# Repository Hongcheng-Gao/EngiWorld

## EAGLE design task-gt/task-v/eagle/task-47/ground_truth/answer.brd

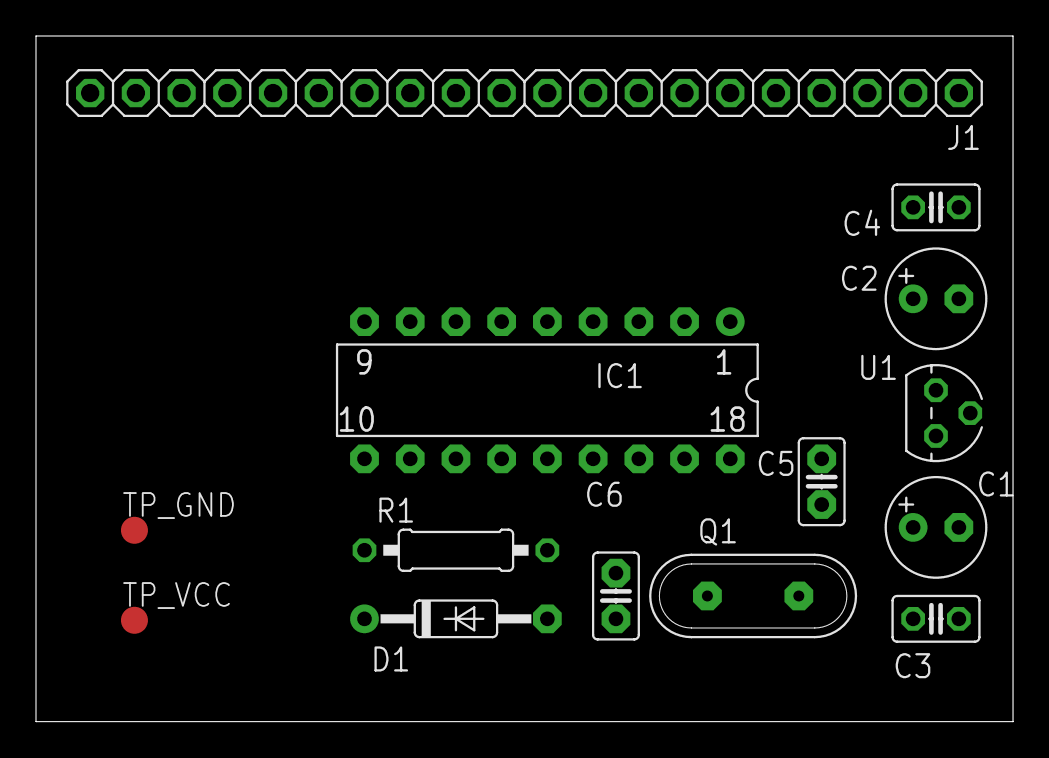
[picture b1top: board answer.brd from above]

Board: 2 copper layers, 54.3 x 38.1 mm, 14 parts (0 on the bottom side), 20 nets, no tracks yet.

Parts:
C1, C2: 10u; E2,5-6
C3, C4: 10n; C025-025X050
C5, C6: 27p; C2,5-2
D1: 1N4148; DO35-10
IC1: 16F84; DIL18
J1: 1X20
Q1: QS
R1: 2.2k; 0207/10
TP_GND: TP15R
TP_VCC: TP15R
U1: 78L05; TO92

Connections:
+12V: C1.+, C3.2, J1.2, U1.3
A0: IC1.17, J1.4
A1: IC1.18, J1.5
A2: IC1.1, J1.6
A3: IC1.2, J1.7
A4: IC1.3, J1.8
B0: IC1.6, J1.9
B1: IC1.7, J1.10
B2: IC1.8, J1.11
B3: IC1.9, J1.12
B4: IC1.10, J1.13
B5: IC1.11, J1.14
B6: IC1.12, J1.15, J1.18
B7: IC1.13, J1.16, J1.17
GND: C1.-, C2.-, C3.1, C4.1, C5.1, C6.1, IC1.5, J1.1, J1.20, TP_GND.TP, U1.2
unnamed: D1.K, IC1.4, J1.19
unnamed: D1.A, R1.1
unnamed: C5.2, IC1.16, Q1.2
unnamed: C6.2, IC1.15, Q1.1
VCC: C2.+, C4.2, IC1.14, J1.3, R1.2, TP_VCC.TP, U1.1

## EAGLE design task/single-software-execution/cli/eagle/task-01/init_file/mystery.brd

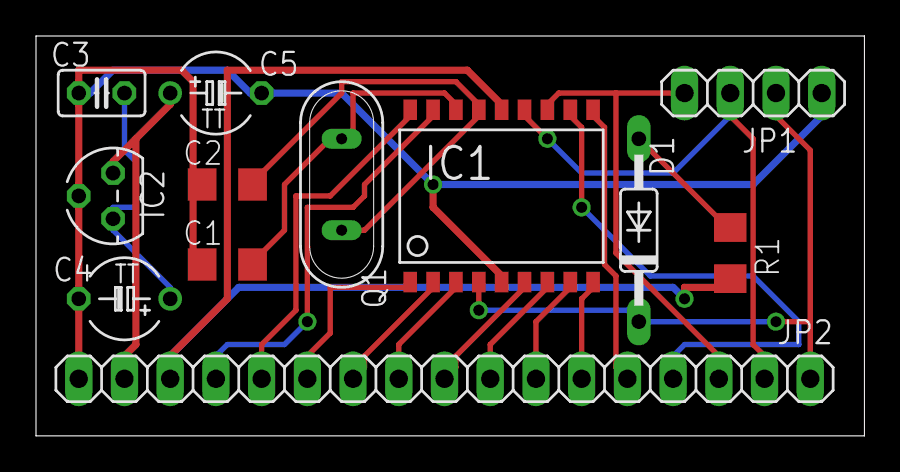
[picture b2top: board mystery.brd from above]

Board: 2 copper layers, 46.0 x 22.2 mm, 12 parts (0 on the bottom side), 21 nets.

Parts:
C1, C2: 30p; C1206
C3: 10n; C025-025X050
C4: 47u/25V; TAP5-45
C5: 47u; TAP5-45
D1: 1N4148; DO35-10
IC1: PIC16F84ASO; SO-18W
IC2: 78L05Z; TO92
JP1: PROG; 1X04
JP2: APPL; 1X17
Q1: QS
R1: 2,2k; R1206

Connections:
+5V: IC1.14, JP2.15, R1.1
GND: C1.1, C2.1, C3.2, C4.-, C5.-, IC1.5, IC2.2, JP1.4, JP2.17
MCLR/PGM: D1.C, IC1.4, JP1.3, JP2.1
unnamed: C3.1, C4.+, IC2.1
unnamed: C1.2, IC1.16, Q1.2
unnamed: C2.2, IC1.15, Q1.1
unnamed: D1.A, R1.2
RA0: IC1.17, JP2.14
RA1: IC1.18, JP2.13
RA2: IC1.1, JP2.12
RA3: IC1.2, JP2.11
RA4: IC1.3, JP2.10
RB0: IC1.6, JP2.9
RB1: IC1.7, JP2.8
RB2: IC1.8, JP2.7
RB3: IC1.9, JP2.6
RB4: IC1.10, JP2.5
RB5: IC1.11, JP2.4
RB6/CLK: IC1.12, JP1.1, JP2.3
RB7/DATA: IC1.13, JP1.2, JP2.2
V+: C5.+, IC2.3, JP2.16
